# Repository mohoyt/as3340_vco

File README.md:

# AS3340 Voltage Controlled Oscillator
A Eurorack VCO powered by AS3340

## Features
* 40mm x 99mm single PCB design (so very cheap to manufacture)
* Lots of standing resistors and diodes to help achieve this (so it's a super crowded PCB)
* See BOM info [here](bom/ibom.html)

## Inputs
* 1v/Oct In
* CV2 In
* FM In
* Sync In (selectable between hard and soft sync with switch and settable between positive hard sync (default) and negative hard sync with a jumper)
* PWM Control In

## Outputs
* Sawtooth
* Square
* Triangle

## Influences
* [Digisound 80 VCO](http://www.digisound80.co.uk/digisound/modules/80-2_files/80-2.pdf)
* [Eddy Bergman's 3340 VCO](https://www.eddybergman.com/2020/01/synthesizer-build-part-18-really-good.html)
* [AI Synthesis' VCO](https://aisynthesis.com/product/ai011-voltage-controlled-oscillator/)

## Status
* First batch of PCBs arrived and 1 built. Working and tunable. 
* Lots of standing resistors to maximise soldering challenges
* 3d printed panel designed (now available in panels folder)
* Use this design at your own risk

## Build notes
* Pay close attention to the iBOM to get the right positioning
* Make sure you do the components under the ICs before you solder the IC sockets
* Start with the shorter components and work your way up (I started with resistors and diodes)
* Do panel components last (and ideally mount on panel before soldering to get best alignment)
* The digisound guide was helpful in tuning. Focus on getting the relationship between 1v/octave at lowish freqs with trimmer 2 while octave switch is off. Then use trimmer 1 to tune with keyboard with the fine tune pot in the middle position. Trimmer 3 can be used to adjust linearity at high freqs. 

## Known Issues
- [x] Some resistor values need updating in BOM
- [ ] Holes for toggle switches are slightly too close together so legs will need bent to fit until footprint is updated. 
- [ ] Footprint for poly timing cap could be much bigger

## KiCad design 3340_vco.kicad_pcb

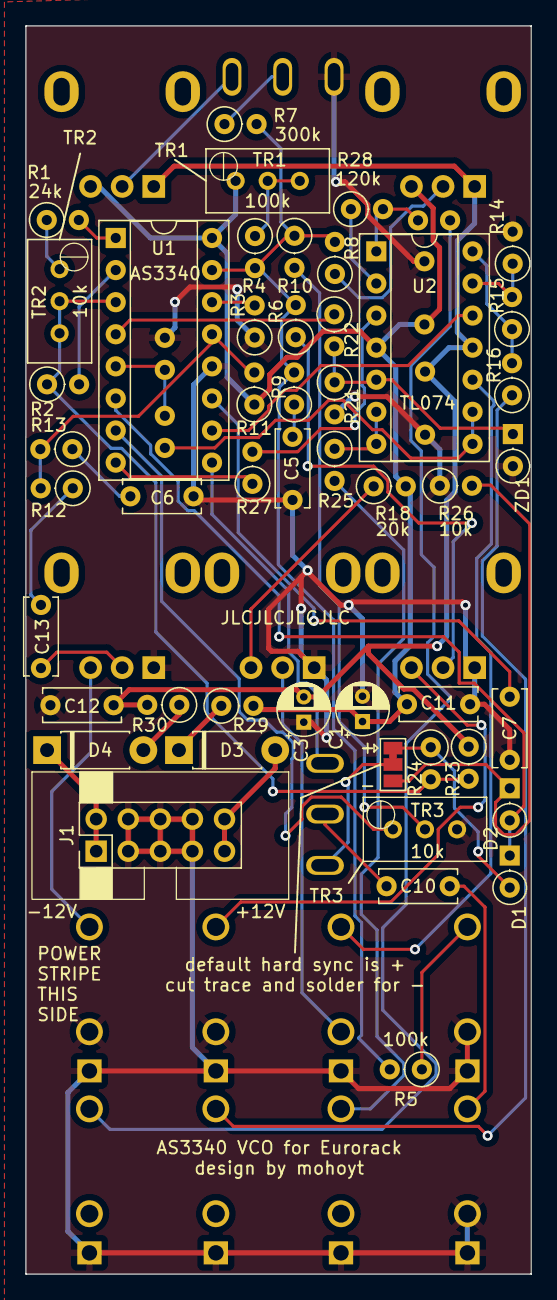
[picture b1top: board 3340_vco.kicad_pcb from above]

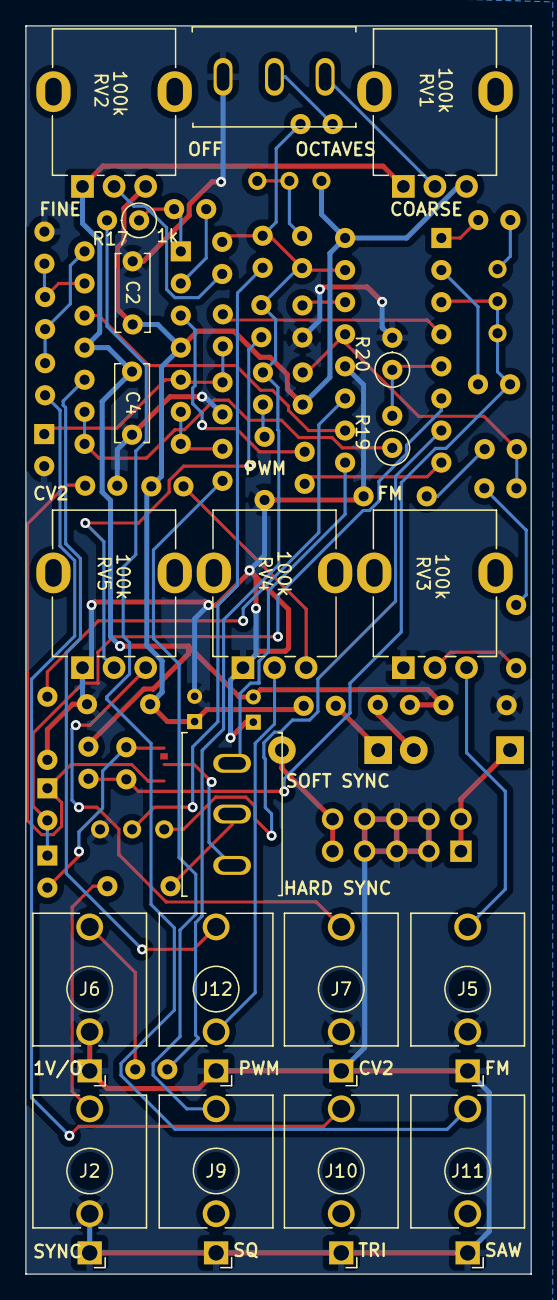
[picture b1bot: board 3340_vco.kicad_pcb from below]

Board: 2 copper layers, 40.0 x 98.8 mm, 68 parts (20 on the bottom side), 54 nets.

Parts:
C1, C3: 47uF; CP_Radial_D4.0mm_P2.00mm
C2, C4, C11, C12: 0.1uF; C_Disc_D6.0mm_W2.5mm_P5.00mm
C5, C6: 10nF; C_Disc_D6.0mm_W2.5mm_P5.00mm
C7: 1nF (styrene); C_Disc_D6.0mm_W2.5mm_P5.00mm
C10: 1nF; C_Disc_D6.0mm_W2.5mm_P5.00mm
C13: 100nF; C_Disc_D6.0mm_W2.5mm_P5.00mm
D1, D2: 1N4148; D_DO-35_SOD27_P2.54mm_Vertical_KathodeUp
D3, D4: 1N5819; D_DO-41_SOD81_P7.62mm_Horizontal
J1: Conn_01x10; PinHeader_2x05_P2.54mm_Vertical_Shroud
J2: SYNC IN; Jack_3.5mm_QingPu_WQP-PJ398SM_Vertical_CircularHoles
J5: FM IN; Jack_3.5mm_QingPu_WQP-PJ398SM_Vertical_CircularHoles
J6: 1V/OCT IN; Jack_3.5mm_QingPu_WQP-PJ398SM_Vertical_CircularHoles
J7: CV2 IN; Jack_3.5mm_QingPu_WQP-PJ398SM_Vertical_CircularHoles
J9: SQ OUT; Jack_3.5mm_QingPu_WQP-PJ398SM_Vertical_CircularHoles
J10: TRI OUT; Jack_3.5mm_QingPu_WQP-PJ398SM_Vertical_CircularHoles
J11: SAW OUT; Jack_3.5mm_QingPu_WQP-PJ398SM_Vertical_CircularHoles
J12: EXT PWM CONTROL IN; Jack_3.5mm_QingPu_WQP-PJ398SM_Vertical_CircularHoles
JP1: POS/NEG SYNC JUMPER; SolderJumper-3_P1.3mm_Bridged12_Pad1.0x1.5mm
R1: 24k; R_Axial_DIN0207_L6.3mm_D2.5mm_P2.54mm_Vertical
R2: 5k6; R_Axial_DIN0207_L6.3mm_D2.5mm_P2.54mm_Vertical
R3: 1k8; R_Axial_DIN0207_L6.3mm_D2.5mm_P2.54mm_Vertical
R4: 270k; R_Axial_DIN0207_L6.3mm_D2.5mm_P2.54mm_Vertical
R5, R6, R14, R27: 100k; R_Axial_DIN0207_L6.3mm_D2.5mm_P2.54mm_Vertical
R7: 300k; R_Axial_DIN0207_L6.3mm_D2.5mm_P2.54mm_Vertical
R8: 3M3; R_Axial_DIN0207_L6.3mm_D2.5mm_P2.54mm_Vertical
R9, R13: 470; R_Axial_DIN0207_L6.3mm_D2.5mm_P2.54mm_Vertical
R10, R12: 1M; R_Axial_DIN0207_L6.3mm_D2.5mm_P2.54mm_Vertical
R11: 1M2; R_Axial_DIN0207_L6.3mm_D2.5mm_P2.54mm_Vertical
R15, R28: 120k; R_Axial_DIN0207_L6.3mm_D2.5mm_P2.54mm_Vertical
R16, R17, R25: 1k; R_Axial_DIN0207_L6.3mm_D2.5mm_P2.54mm_Vertical
R18: 20k; R_Axial_DIN0207_L6.3mm_D2.5mm_P2.54mm_Vertical
R19, R20, R21: 47k; R_Axial_DIN0207_L6.3mm_D2.5mm_P2.54mm_Vertical
R22: 2k; R_Axial_DIN0207_L6.3mm_D2.5mm_P2.54mm_Vertical
R23: 680; R_Axial_DIN0207_L6.3mm_D2.5mm_P2.54mm_Vertical
R24, R26: 10k; R_Axial_DIN0207_L6.3mm_D2.5mm_P2.54mm_Vertical
R29, R30: 10; R_Axial_DIN0207_L6.3mm_D2.5mm_P2.54mm_Vertical
RV1, RV2, RV3, RV4, RV5: 100k; Potentiometer_Alpha_RD901F-40-00D_Single_Vertical
SW1: OCTAVES; SW_SPST_SPDT
SW2: SYNC_TYPE; SW_SPST_SPDT
TR1: 100k; Potentiometer_Bourns_3296W_Vertical
TR2, TR3: 10k; Potentiometer_Bourns_3296W_Vertical
U1: AS3340; DIP-16_W7.62mm_Socket
U2: TL074; DIP-14_W7.62mm_Socket
ZD1: 10V Zener Diode; D_DO-35_SOD27_P2.54mm_Vertical_KathodeUp

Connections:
1V/OCT IN: J6.T, R5.1
+12V: C1.1, C2.1, C11.1, R11.1, R18.2, R29.2, RV1.3, RV2.3, TR1.1, U1.16 (VCC), U2.4 (V+)
-12V: C3.2, C4.2, C12.2, R23.1, R30.2, RV1.1, RV2.1, U2.11 (V-)
CV2 IN: J7.T, RV5.3
EXT PWM CONTROL IN: J12.T, U2.10 (+)
FM IN: J5.T, RV3.3
GND: C1.2, C2.2, C3.1, C4.1, C5.1, C6.1, C7.1, C11.2, C12.1, J1.3, J1.4, J1.5, J1.6, J1.7, J1.8, J2.S, J2.TN, J5.S, J5.TN, J6.S, J6.TN, J7.S, J7.TN, J9.S, J10.S, J11.S, J12.S, R3.1, R14.2, R20.2, R21.2, R26.1, RV3.1, RV4.1, RV5.1, SW1.1 (A), TR3.3, U1.12 (GND), ZD1.2 (A)
NEG HARD SYNC IN: D2.1 (K), JP1.3 (B), R26.2
unnamed: C5.2, R9.1
unnamed: C6.2, R13.1
unnamed: C13.1, RV3.2
unnamed: C13.2, R12.1
unnamed: D1.1 (K), D2.2 (A), U1.6 (VHSI)
unnamed: D3.2 (A), J1.9, J1.10
unnamed: D3.1 (K), R29.1
unnamed: D4.2 (A), R30.1
unnamed: D4.1 (K), J1.1, J1.2
unnamed: J12.TN, RV4.2
unnamed: JP1.2 (C), SW2.1 (A)
unnamed: R1.1, TR2.1
unnamed: R4.1, TR1.2, TR1.3
unnamed: R6.1, RV5.2
unnamed: R8.1, RV2.2
unnamed: R10.2, TR3.2
unnamed: R15.1, R16.2, U2.14
unnamed: R17.1, R28.2, U2.1
unnamed: R18.1, RV4.3
unnamed: R7.1, SW1.2 (B)
unnamed: RV1.2, SW1.3 (C)
unnamed: C10.2, SW2.2 (B)
unnamed: C7.2, U1.11 (CAP)
unnamed: R1.2, U1.1 (SCALE1)
unnamed: R2.2, U1.2 (SCALE2)
unnamed: R2.1, R23.2, R24.2, TR2.2, TR2.3, U1.3 (VEE)
unnamed: R4.2, R5.2, R6.2, R7.2, R8.2, R9.2, R10.1, U1.15 (VFCI)
unnamed: TR3.1, U1.7 (VHFT)
unnamed: R11.2, R12.2, R13.2, U1.13 (VLFI)
unnamed: R22.1, U1.4 (VP)
unnamed: R19.2, R20.1, U1.5 (VPWM)
unnamed: R3.2, U1.14 (VS)
unnamed: R27.1, U1.8 (VSO)
unnamed: U1.10 (VTO), U2.12 (+)
unnamed: R27.2, U2.3 (+)
unnamed: R28.1, U2.2 (-)
unnamed: R21.1, R22.2, U2.5 (+), ZD1.1 (K)
unnamed: R25.1, U2.6 (-), U2.7
unnamed: R19.1, U2.8, U2.9 (-)
unnamed: R14.1, R15.2, U2.13 (-)
POS HARD SYNC IN: D1.2 (A), JP1.1 (A), R24.1
SAW OUT: J11.T, R17.2
SOFT SYNC IN: SW2.3 (C), U1.9 (VSSI)
SQ OUT: J9.T, R25.2
SYNC IN: C10.1, J2.T
TRI OUT: J10.T, R16.1

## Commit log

2023-10-25 Added LICENSE
2023-10-25 v1 added
2023-10-25 img fixed
2023-10-26 BOM added
2023-10-26 Readme updated
2023-11-10 BOM updated with correct resistor values
2023-11-10 readme updated and images added
2025-01-22 3D printed panel added
